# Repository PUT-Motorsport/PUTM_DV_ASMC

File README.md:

# ASMC: Autonomous System Main Controller

## Project Overview
The **ASMC (Autonomous System Main Controller)** is a central electronic control unit designed for a Formula Student racing vehicle. Its primary objective is to integrate the critical subsystems required for autonomous operation in compliance with the **Formula Student Rules 2026**. 

This board serves as a robust interface between the high-level autonomous compute unit and the vehicle's hardware, ensuring safety, reliable power distribution, and real-time status signaling.

## Key Functionalities

### 1. Power Management & Distribution
* **Peripheral Supply**: Provides regulated and protected power to sensors, actuators, and processing units necessary for the Autonomous System (AS).
* **LVS Compliance**: Operates within the Low Voltage System (LVS) limits (max 60V DC) and ensures proper grounding to the chassis.
* **Overcurrent Protection**: Integrated protection for all connected devices to prevent hardware failure during dynamic disciplines.

### 2. Autonomous System Signaling (ASSI & AMI)
* **ASSI Control**: Drives three Autonomous System Status Indicators (ASSI) positioned on the sides and rear of the vehicle.
* **Visual Logic**: Implements mandatory lighting patterns (e.g., 2–5 Hz flashing for "Driving" and "Emergency" states).
* **Acoustic Warning**: Manages the intermittent sound signal (80–90 dBA) required during the "AS Emergency" state.
* **Mission Selection**: Interfaces with the Autonomous Mission Indicator (AMI) to allow manual mission selection and status feedback without external tools.

### 3. Safety & Braking Interface (ASB/EBS)
* **EBS Data Processing**: Receives and processes critical data from the Emergency Brake System (EBS).
* **SCS Monitoring**: Continuously monitors System Critical Signals (SCS). Any failure (e.g., open circuit or data corruption) triggers a safe state transition within <500ms.
* **SDC & RES Integration**: Interfaces with the Shutdown Circuit (SDC) and the Remote Emergency System (RES) to allow for immediate vehicle shutdown.

## Technical Compliance
Designed according to the **T14 (Autonomous System)** and **T15 (Autonomous System Brake)** sections of the FS 2026 rulebook.

* **AS Status Flowchart**: The board logic follows the mandatory state machine (Off, Ready, Driving, Emergency, Finished).
* **Failsafe Design**: Ensures that loss of power or signal defaults the vehicle to an "AS Emergency" state, engaging the mechanical brakes.
* **Data Logging**: Provides necessary signal outputs to the official Formula Student Data Logger for competition transparency.

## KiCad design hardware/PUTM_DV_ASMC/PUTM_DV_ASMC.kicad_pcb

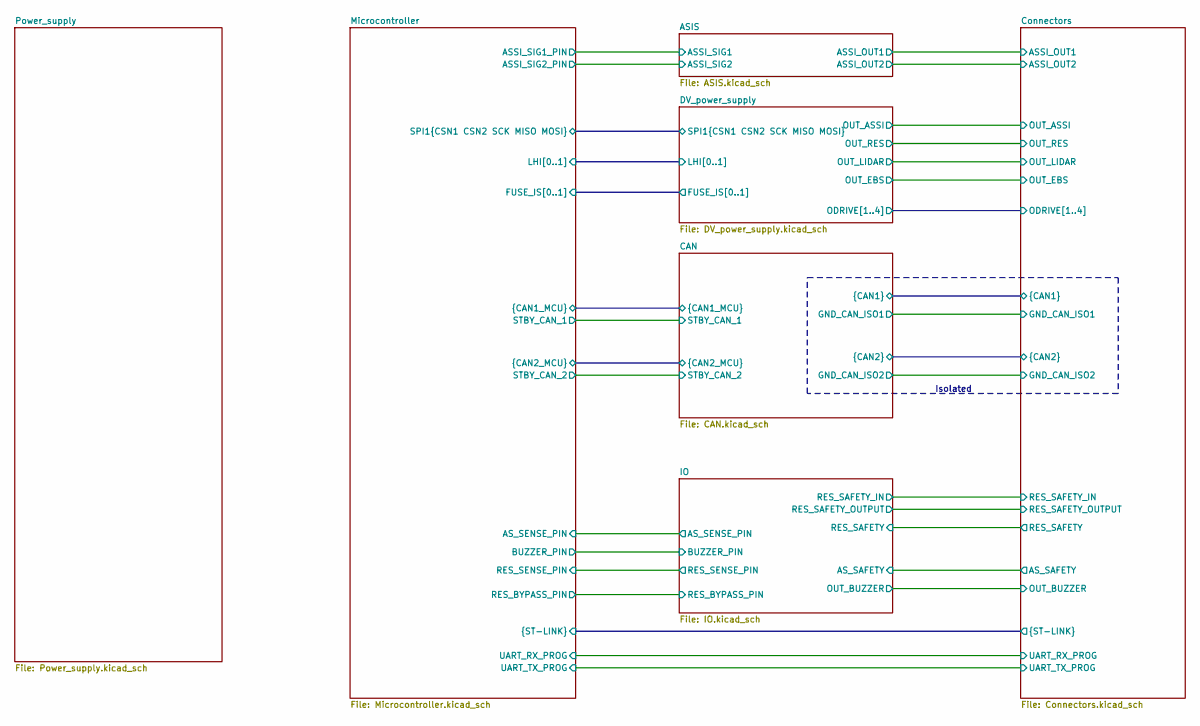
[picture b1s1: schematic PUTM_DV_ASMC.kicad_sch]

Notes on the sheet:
Isolated

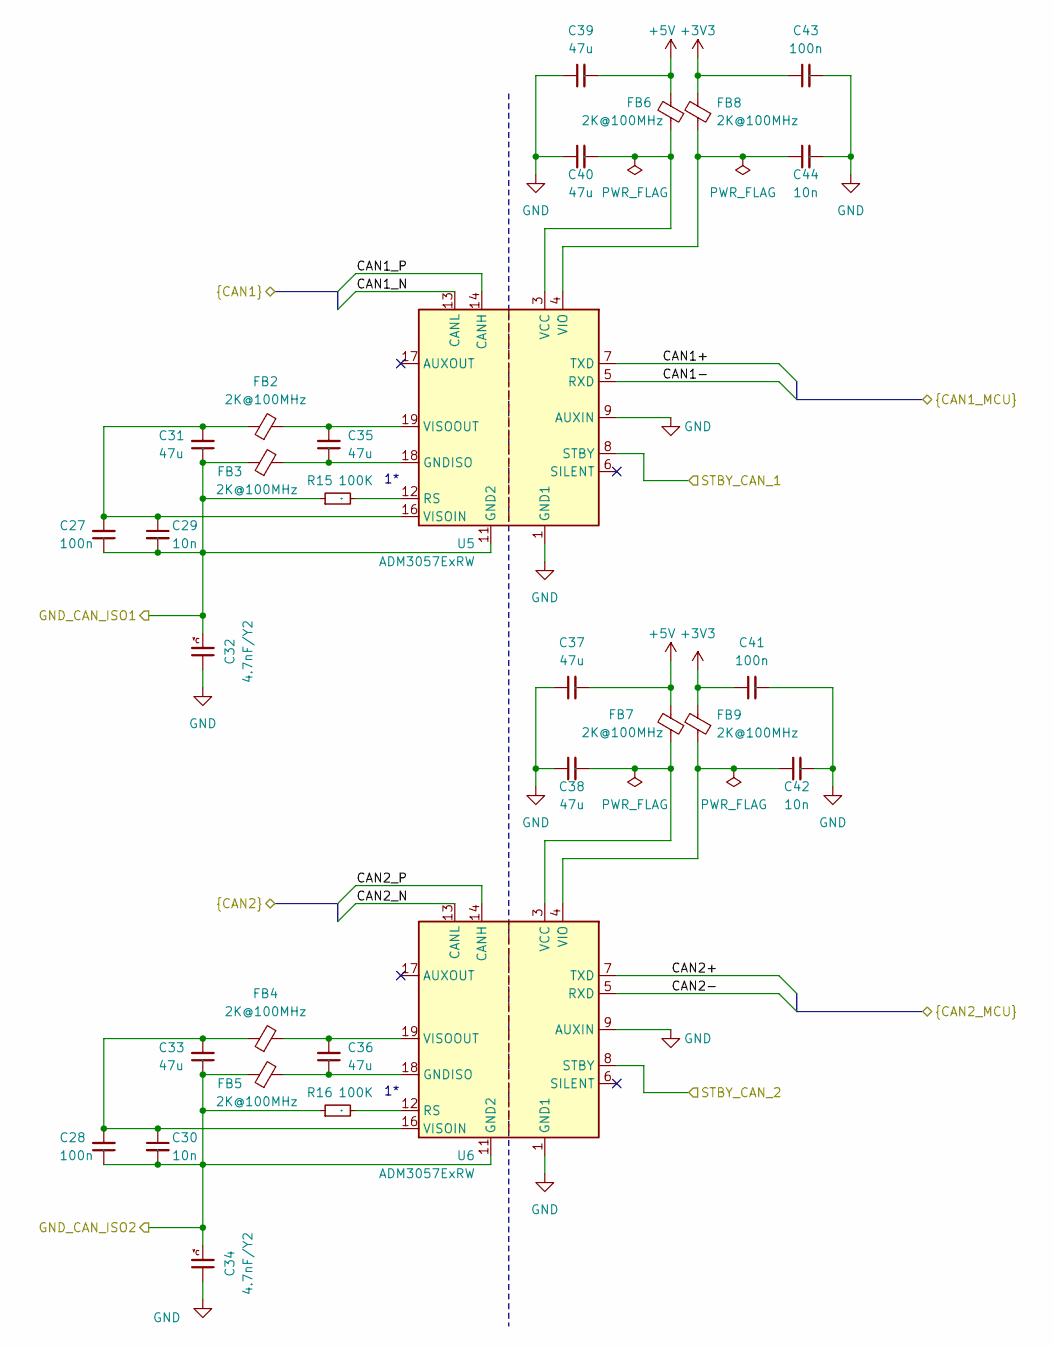
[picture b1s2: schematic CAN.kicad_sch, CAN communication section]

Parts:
C27, C28, C41, C43: 100n; C_0603_1608Metric_Pad1.08x0.95mm_HandSolder; Mouser Part Number .
C29, C30, C42, C44: 10n; C_0603_1608Metric_Pad1.08x0.95mm_HandSolder; Mouser Part Number .
C31, C33, C35, C36, C37, C38, C39, C40: 47u; C_0805_2012Metric_Pad1.18x1.45mm_HandSolder; Mouser Part Number .
C32, C34: 4.7nF/Y2; CAPC5728X280N; Mouser Part Number 791-S252B222K502CT
FB2, FB3, FB4, FB5, FB6, FB7, FB8, FB9: 2K@100MHz; L_0805_2012Metric_Pad1.05x1.20mm_HandSolder; Mouser Part Number 623-2508052027Y1
R15, R16: 100K; R_0603_1608Metric_Pad0.98x0.95mm_HandSolder; Mouser Part Number .
U5, U6: ADM3057ExRW; SOIC-20W_7.5x12.8mm_P1.27mm; Mouser Part Number 584-ADM3057EBRWZ

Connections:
+3V3: C41.1, C43.1, FB8.2, FB9.2; also elsewhere on the board
+5V: C37.2, C39.2, FB6.2, FB7.2; also elsewhere on the board
/CAN/CAN1+: U5.7 (TXD); also elsewhere on the board
/CAN/CAN1-: U5.5 (RXD); also elsewhere on the board
/CAN/CAN1_N: U5.13 (CANL); also elsewhere on the board
/CAN/CAN1_P: U5.14 (CANH); also elsewhere on the board
/CAN/CAN2+: U6.7 (TXD); also elsewhere on the board
/CAN/CAN2-: U6.5 (RXD); also elsewhere on the board
/CAN/CAN2_N: U6.13 (CANL); also elsewhere on the board
/CAN/CAN2_P: U6.14 (CANH); also elsewhere on the board
/CAN/GND_CAN_ISO1: C27.1, C29.2, C31.1, C32.2, FB3.1, R15.1, U5.11 (GND2), U5.15 (GND2); also elsewhere on the board
/CAN/GND_CAN_ISO2: C28.1, C30.2, C33.1, C34.2, FB5.1, R16.1, U6.11 (GND2), U6.15 (GND2); also elsewhere on the board
/CAN/STBY_CAN_1: U5.8 (STBY); also elsewhere on the board
/CAN/STBY_CAN_2: U6.8 (STBY); also elsewhere on the board
GND: C32.1, C34.1, C37.1, C38.1, C39.1, C40.1, C41.2, C42.2, C43.2, C44.2, U5.1 (GND1), U5.2 (GND1), U5.9 (AUXIN), U5.10 (GND1), U6.1 (GND1), U6.2 (GND1), U6.9 (AUXIN), U6.10 (GND1); also elsewhere on the board
unnamed: C35.1, FB3.2, U5.18 (GNDISO), U5.20 (GNDISO)
unnamed: C36.1, FB5.2, U6.18 (GNDISO), U6.20 (GNDISO)
unnamed: R15.2, U5.12 (RS)
unnamed: C40.2, FB6.1, U5.3 (VCC)
unnamed: C44.1, FB8.1, U5.4 (VIO)
unnamed: C27.2, C29.1, C31.2, FB2.1, U5.16 (VISOIN)
unnamed: C35.2, FB2.2, U5.19 (VISOOUT)
unnamed: R16.2, U6.12 (RS)
unnamed: C38.2, FB7.1, U6.3 (VCC)
unnamed: C42.1, FB9.1, U6.4 (VIO)
unnamed: C28.2, C30.1, C33.2, FB4.1, U6.16 (VISOIN)
unnamed: C36.2, FB4.2, U6.19 (VISOOUT)

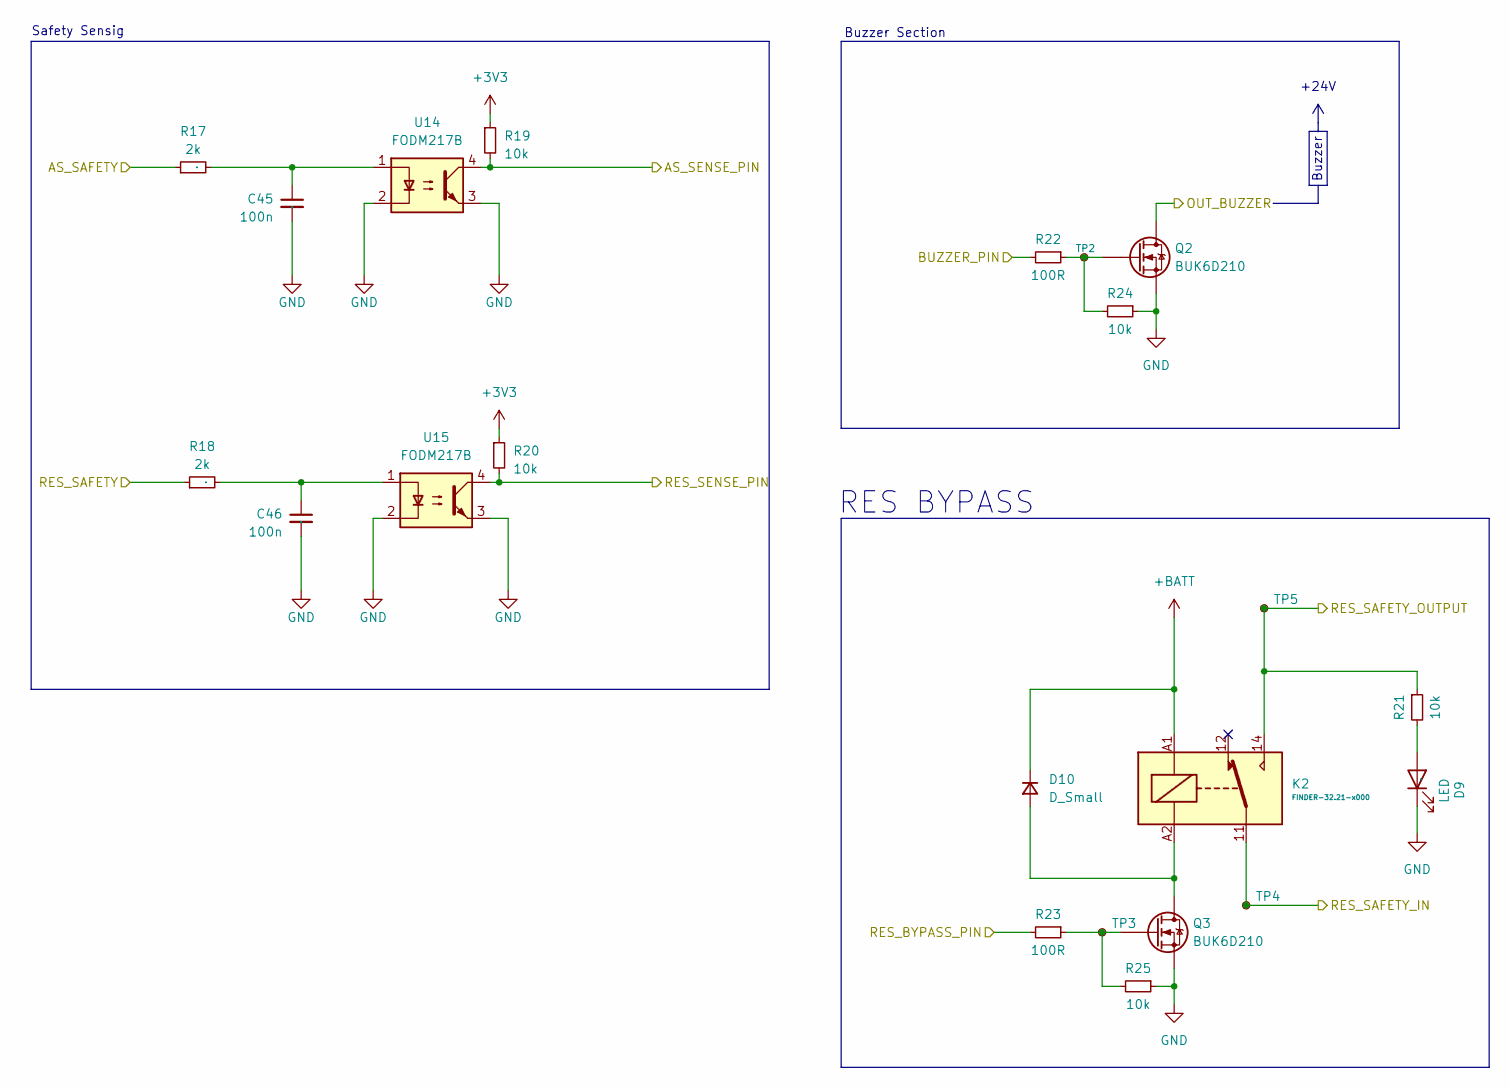
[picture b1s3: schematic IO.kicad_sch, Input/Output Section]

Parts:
C45, C46: 100n; C_0603_1608Metric_Pad1.08x0.95mm_HandSolder; Mouser Part Number .
D9: LED; LED_0603_1608Metric_Pad1.05x0.95mm_HandSolder; Mouser Part Number .
D10: D_Small; D_SOD-323_HandSoldering
K2: FINDER-32.21-x000; Relay_SPDT_Finder_32.21-x000
Q2, Q3: BUK6D210; Diodes_UDFN2020-6_Type-F
R17, R18: 2k; R_0603_1608Metric_Pad0.98x0.95mm_HandSolder; Mouser Part Number .
R19, R20: 10k; R_0603_1608Metric_Pad0.98x0.95mm_HandSolder; Mouser Part Number .
R21: 10k; R_1206_3216Metric_Pad1.30x1.75mm_HandSolder
R22, R23: 100R; R_0603_1608Metric
R24, R25: 10k; R_0603_1608Metric
TP2: TestPoint_Small; TestPoint_Pad_D1.0mm
TP3, TP4, TP5: TestPoint_Small
U14, U15: FODM217B; SOP-4_4.4x2.6mm_P1.27mm; Mouser Part Number 512-FODM217B

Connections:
+3V3: R19.1, R20.1; also elsewhere on the board
+BATT: D10.1 (K), K2.A1; also elsewhere on the board
/Connectors/AS_SAFETY: R17.1; also elsewhere on the board
/Connectors/OUT_BUZZER: Q2.1 (D), Q2.2 (D), Q2.5 (D), Q2.6 (D), Q2.7 (D); also elsewhere on the board
/Connectors/RES_SAFETY: R18.1; also elsewhere on the board
/Connectors/RES_SAFETY_IN: K2.11, TP4.1; also elsewhere on the board
/Connectors/RES_SAFETY_OUTPUT: K2.14, R21.1, TP5.1; also elsewhere on the board
/IO/AS_SENSE_PIN: R19.2, U14.4; also elsewhere on the board
/IO/BUZZER_PIN: R22.2; also elsewhere on the board
/IO/RES_BYPASS_PIN: R23.2; also elsewhere on the board
/IO/RES_SENSE_PIN: R20.2, U15.4; also elsewhere on the board
GND: C45.2, C46.2, D9.1 (K), Q2.4 (S), Q2.8 (S), Q3.4 (S), Q3.8 (S), R24.1, R25.1, U14.2, U14.3, U15.2, U15.3; also elsewhere on the board
unnamed: C45.1, R17.2, U14.1
unnamed: C46.1, R18.2, U15.1
unnamed: D9.2 (A), R21.2
unnamed: D10.2 (A), K2.A2, Q3.1 (D), Q3.2 (D), Q3.5 (D), Q3.6 (D), Q3.7 (D)
unnamed: Q2.3 (G), R22.1, R24.2, TP2.1 (1_1)
unnamed: Q3.3 (G), R23.1, R25.2, TP3.1

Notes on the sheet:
+24V
Buzzer Section
Buzzer
Safety Sensig
RES BYPASS

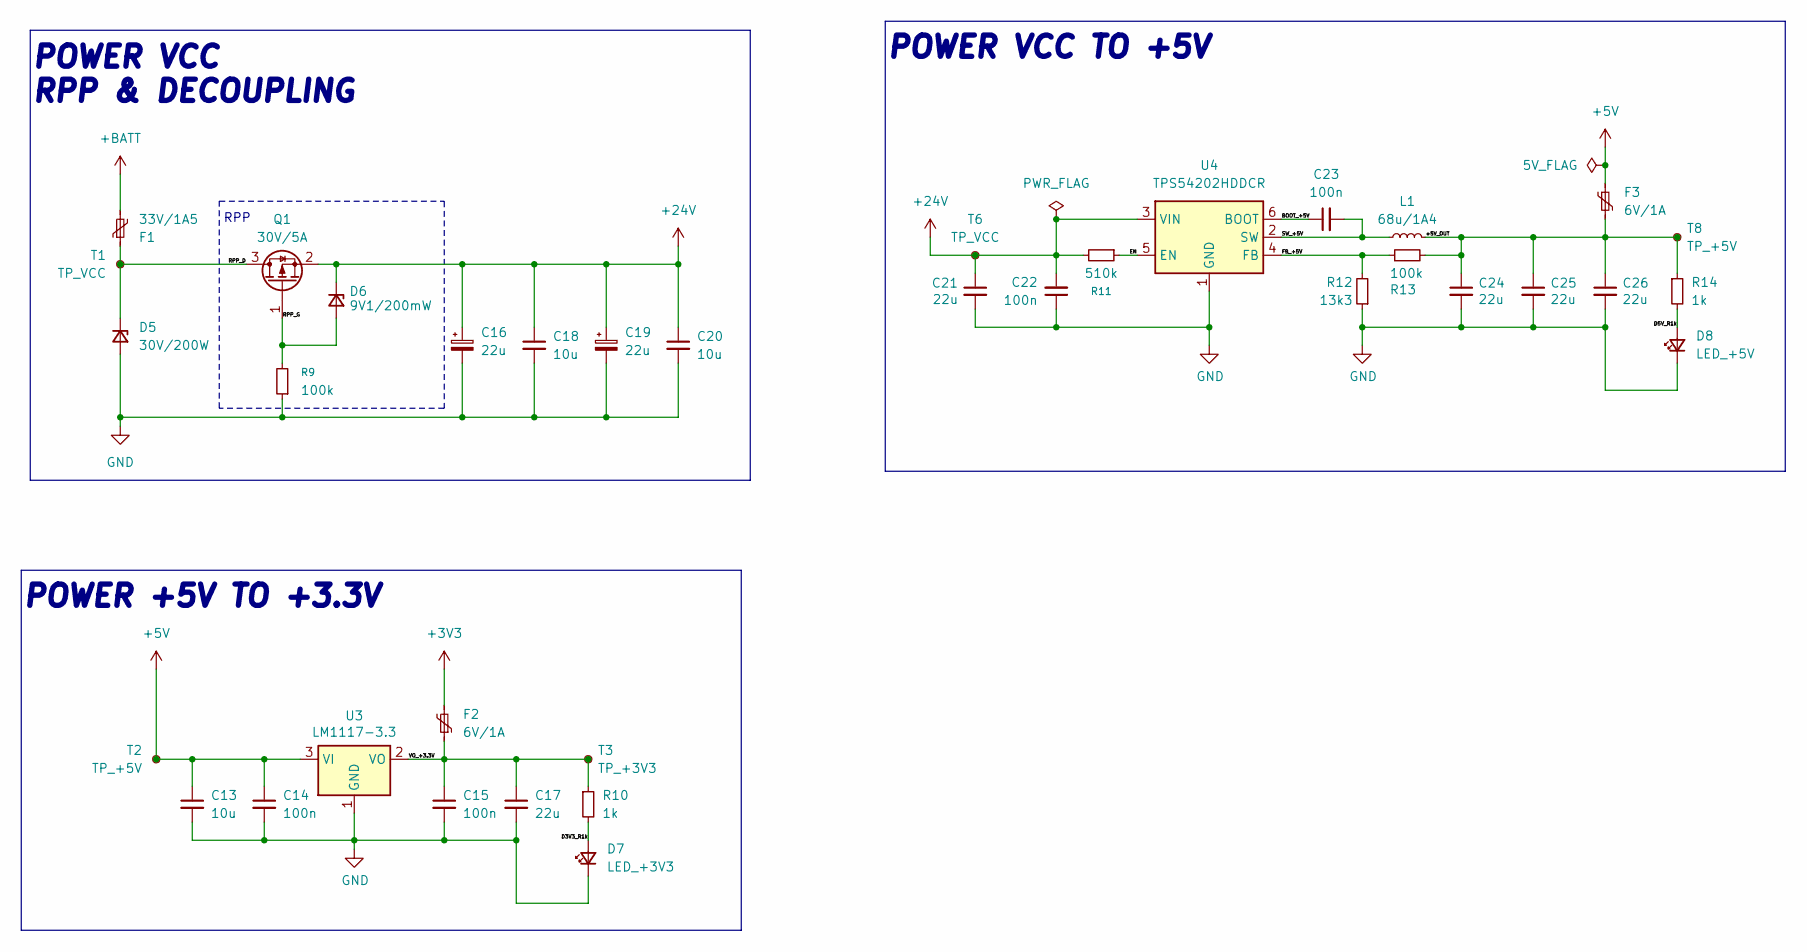
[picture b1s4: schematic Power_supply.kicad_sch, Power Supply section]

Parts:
C13, C18, C20: 10u; C_0805_2012Metric_Pad1.18x1.45mm_HandSolder; Mouser Part Number 81-GRM21BR61H106KE3L
C14, C15, C23: 100n; C_0603_1608Metric_Pad1.08x0.95mm_HandSolder; Mouser Part Number 81-GCJ188R71H104KA2D
C16, C19: 22u; CP_Elec_5x5.8; Mouser Part Number 647-UCM1H220MCL1GS
C17: 22u; C_0805_2012Metric_Pad1.18x1.45mm_HandSolder; Mouser Part Number 810-C2012X5R1V226MAC
C21, C24, C25, C26: 22u; C_0805_2012Metric_Pad1.18x1.45mm_HandSolder; Manufacturer_Part_Number CL21A107MQYNNWE; Mouser Part Number 810-C2012X5R1V226MAC
C22: 100n; C_0603_1608Metric_Pad1.08x0.95mm_HandSolder; Manufacturer_Part_Number C0603C104J3RACTU; Mouser Part Number 81-GCJ188R71H104KA2D
D5: 30V/200W; D_SOD-123; Mouser Part Number 750-TV02W260-G
D6: 9V1/200mW; D_SOD-323_HandSoldering; Mouser Part Number 833-MMXZ5239B-TP
D7: LED_+3V3; LED_0603_1608Metric_Pad1.05x0.95mm_HandSolder
D8: LED_+5V; LED_0603_1608Metric_Pad1.05x0.95mm_HandSolder
F1: 33V/1A5; Fuse_2920_7451Metric_Pad2.10x5.45mm_HandSolder; Mouser Part Number 530-0ZCF0075AF2C
F2, F3: 6V/1A; Fuse_0805_2012Metric_Pad1.15x1.40mm_HandSolder; Mouser Part Number 650-PICOSMDC050S-2
L1: 68u/1A4; L_TDK_VLS6045EX_VLS6045AF; Mouser Part Number 810-VLS6045EX-680M
Q1: 30V/5A; SOT-23-3; Mouser Part Number 78-SI2347DS-T1-GE3
R9: 100k; R_0603_1608Metric_Pad0.98x0.95mm_HandSolder; Mouser Part Number 71-CRCW0603100KFKEAH
R10, R14: 1k; R_0603_1608Metric_Pad0.98x0.95mm_HandSolder; Mouser Part Number 71-CRCW0603-1.0K-E3
R11: 510k; R_0603_1608Metric_Pad0.98x0.95mm_HandSolder; Mouser Part Number 71-CRCW0603J-510K-E3
R12: 13k3; R_0603_1608Metric_Pad0.98x0.95mm_HandSolder; Manufacturer_Part_Number RT0603DRE0713K3L; Mouser Part Number 71-CRCW0603-13.3K-E3
R13: 100k; R_0603_1608Metric_Pad0.98x0.95mm_HandSolder; Manufacturer_Part_Number RT0603DRE07100KL; Mouser Part Number 71-CRCW0603100KFKEAH
T1, T6: TP_VCC; TestPoint_Pad_1.0x1.0mm
T2, T8: TP_+5V; TestPoint_Pad_1.0x1.0mm
T3: TP_+3V3; TestPoint_Pad_1.0x1.0mm
U3: LM1117-3.3; SOT-223-3_TabPin2; Mouser Part Number 926-LM1117MPX3.3NOPB
U4: TPS54202HDDCR; SOT-23-6_Handsoldering; Mouser Part Number 595-TPS54202HDDCR

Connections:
+3V3: F2.2; also elsewhere on the board
+5V: C13.1, C14.1, F3.1, T2.1 (1_1), U3.3 (VI); also elsewhere on the board
+24V: C16.1, C18.1, C19.1, C20.1, C21.1, C22.2, D6.1 (K), Q1.2 (S), R11.2, T6.1 (1_1), U4.3 (VIN)
+BATT: F1.2; also elsewhere on the board
/Power_supply/+5V_OUT: C24.1, C25.1, C26.1, F3.2, L1.2, R13.2, R14.1, T8.1 (1_1)
/Power_supply/BOOT_+5V: C23.1, U4.6 (BOOT)
/Power_supply/D3V3_R1k: D7.2 (A), R10.2
/Power_supply/D5V_R1k: D8.2 (A), R14.2
/Power_supply/EN: R11.1, U4.5 (EN)
/Power_supply/FB_+5V: R12.2, R13.1, U4.4 (FB)
/Power_supply/RPP_D: D5.1 (K), F1.1, Q1.3 (D), T1.1 (1_1)
/Power_supply/RPP_G: D6.2 (A), Q1.1 (G), R9.2
/Power_supply/SW_+5V: C23.2, L1.1, U4.2 (SW)
/Power_supply/VO_+3.3V: C15.1, C17.1, F2.1, R10.1, T3.1 (1_1), U3.2 (VO)
GND: C13.2, C14.2, C15.2, C16.2, C17.2, C18.2, C19.2, C20.2, C21.2, C22.1, C24.2, C25.2, C26.2, D5.2 (A), D7.1 (K), D8.1 (K), R9.1, R12.1, U3.1 (GND), U4.1 (GND); also elsewhere on the board

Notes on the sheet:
POWER +5V TO +3.3V
POWER VCC RPP & DECOUPLING
POWER VCC TO +5V
RPP

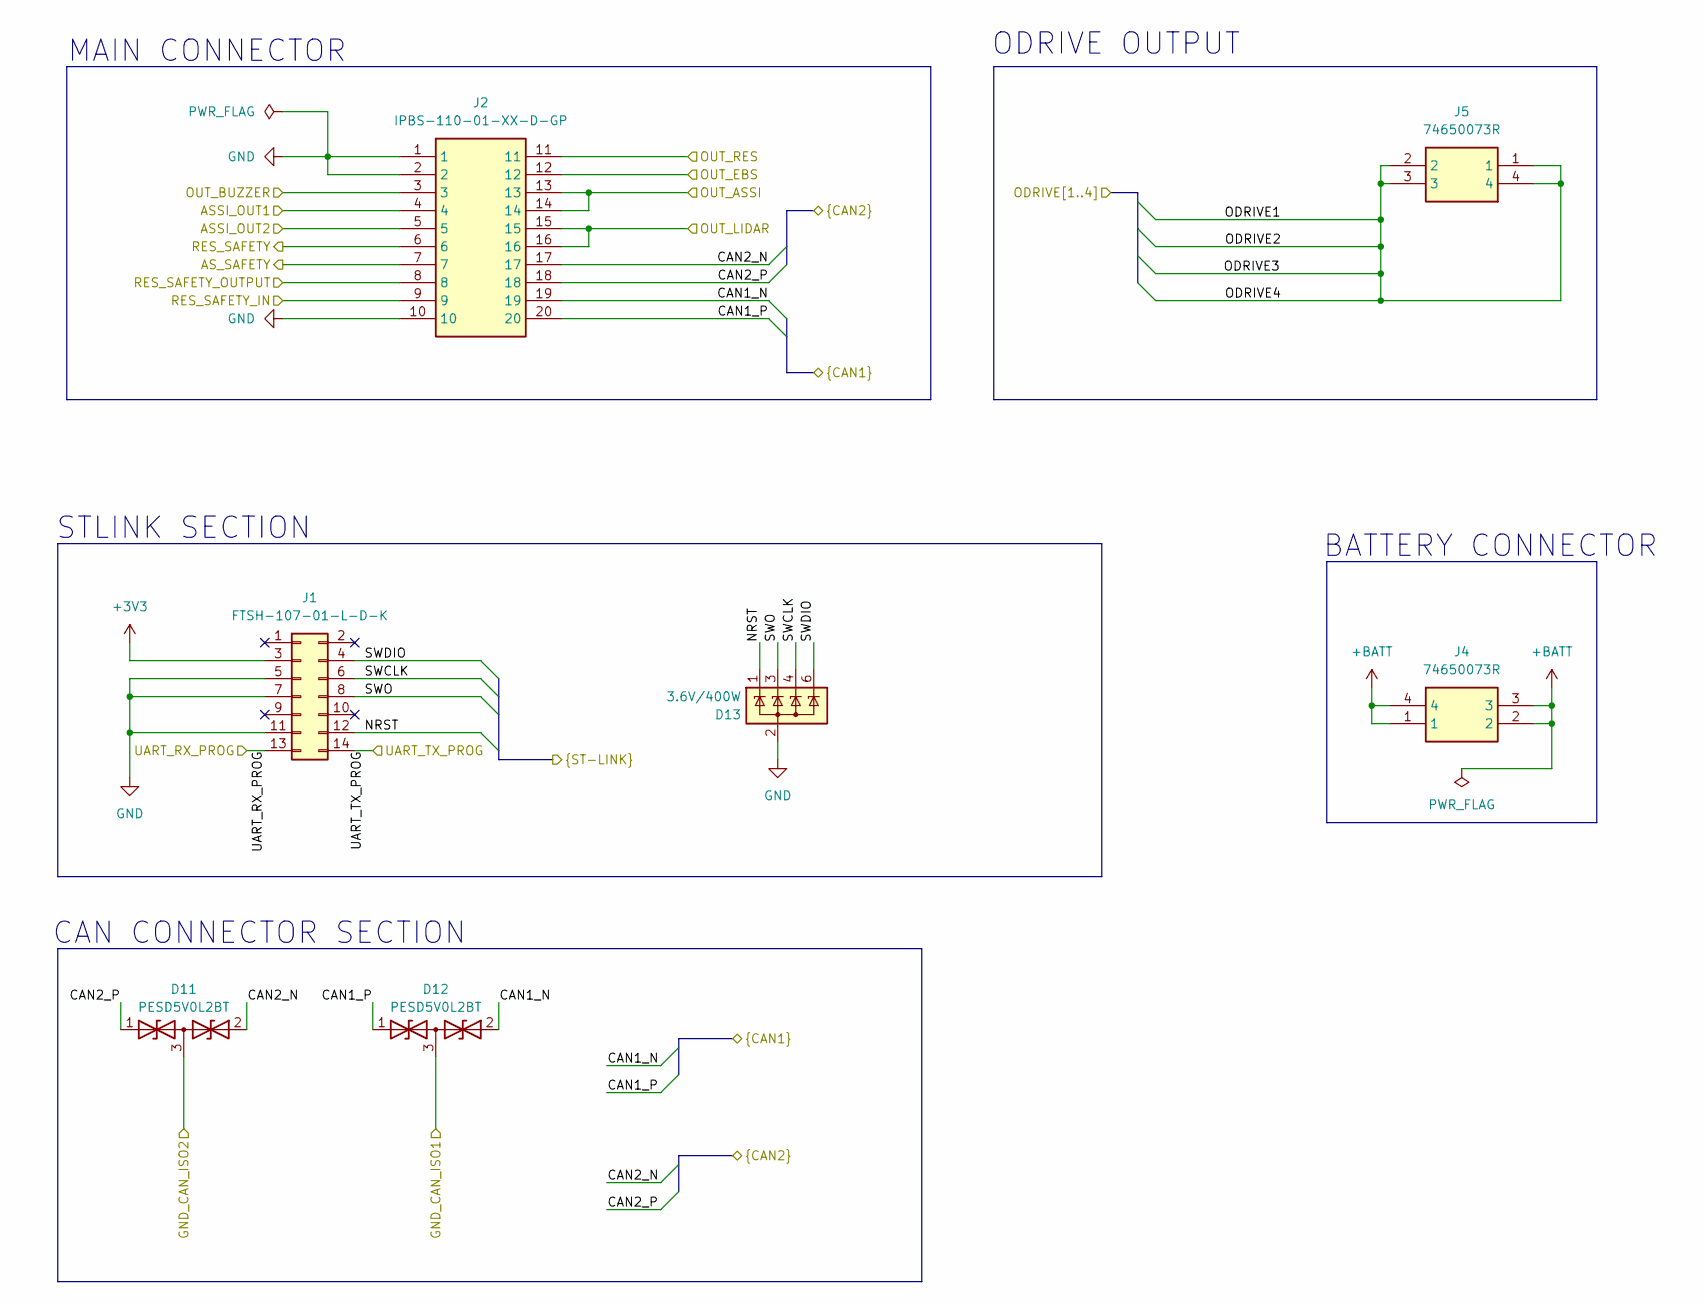
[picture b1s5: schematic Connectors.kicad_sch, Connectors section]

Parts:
D11, D12: PESD5V0L2BT; SOT-23_Handsoldering; Mouser Part Number 771-PESD5V0L2BT-QR
D13: 3.6V/400W; SOT-23-6; Manufacturer_Part_Number ESDS304DBVR; Mouser Part Number 595-ESDS304DBVR
J1: FTSH-107-01-L-D-K; FTSH-107-XX-YYY-D-K; Mouser Part Number 200-FTSH10701LDK
J2: IPBS-110-01-XX-D-GP; IPBS11001TDGP; PARTREV M; Mouser Part Number 200-IPBS11001TDGP
J4, J5: 74650073R; Mouser Part Number 710-74650073R

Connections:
+3V3: J1.3; also elsewhere on the board
+BATT: J4.1, J4.2, J4.3, J4.4; also elsewhere on the board
/ASIS/ASSI_OUT1: J2.4; also elsewhere on the board
/ASIS/ASSI_OUT2: J2.5; also elsewhere on the board
/CAN/CAN1_N: D12.2 (A2), J2.19; also elsewhere on the board
/CAN/CAN1_P: D12.1 (A1), J2.20; also elsewhere on the board
/CAN/CAN2_N: D11.2 (A2), J2.17; also elsewhere on the board
/CAN/CAN2_P: D11.1 (A1), J2.18; also elsewhere on the board
/CAN/GND_CAN_ISO1: D12.3 (common); also elsewhere on the board
/CAN/GND_CAN_ISO2: D11.3 (common); also elsewhere on the board
/Connectors/AS_SAFETY: J2.7; also elsewhere on the board
/Connectors/NRST: D13.1 (A), J1.12; also elsewhere on the board
/Connectors/ODRIVE4: J5.1, J5.2, J5.3, J5.4; also elsewhere on the board
/Connectors/OUT_ASSI: J2.13, J2.14; also elsewhere on the board
/Connectors/OUT_BUZZER: J2.3; also elsewhere on the board
/Connectors/OUT_EBS: J2.12; also elsewhere on the board
/Connectors/OUT_LIDAR: J2.15, J2.16; also elsewhere on the board
/Connectors/OUT_RES: J2.11; also elsewhere on the board
/Connectors/RES_SAFETY: J2.6; also elsewhere on the board
/Connectors/RES_SAFETY_IN: J2.9; also elsewhere on the board
/Connectors/RES_SAFETY_OUTPUT: J2.8; also elsewhere on the board
/Connectors/SWCLK: D13.4 (A), J1.6; also elsewhere on the board
/Connectors/SWDIO: D13.6 (A), J1.4; also elsewhere on the board
/Connectors/SWO: D13.3 (A), J1.8; also elsewhere on the board
/Connectors/UART_RX_PROG: J1.13; also elsewhere on the board
/Connectors/UART_TX_PROG: J1.14; also elsewhere on the board
GND: D13.2 (K), D13.5 (NC), J1.5, J1.7, J1.11, J2.1, J2.2, J2.10; also elsewhere on the board

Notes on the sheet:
BATTERY CONNECTOR
STLINK SECTION
CAN CONNECTOR SECTION
MAIN CONNECTOR
ODRIVE OUTPUT

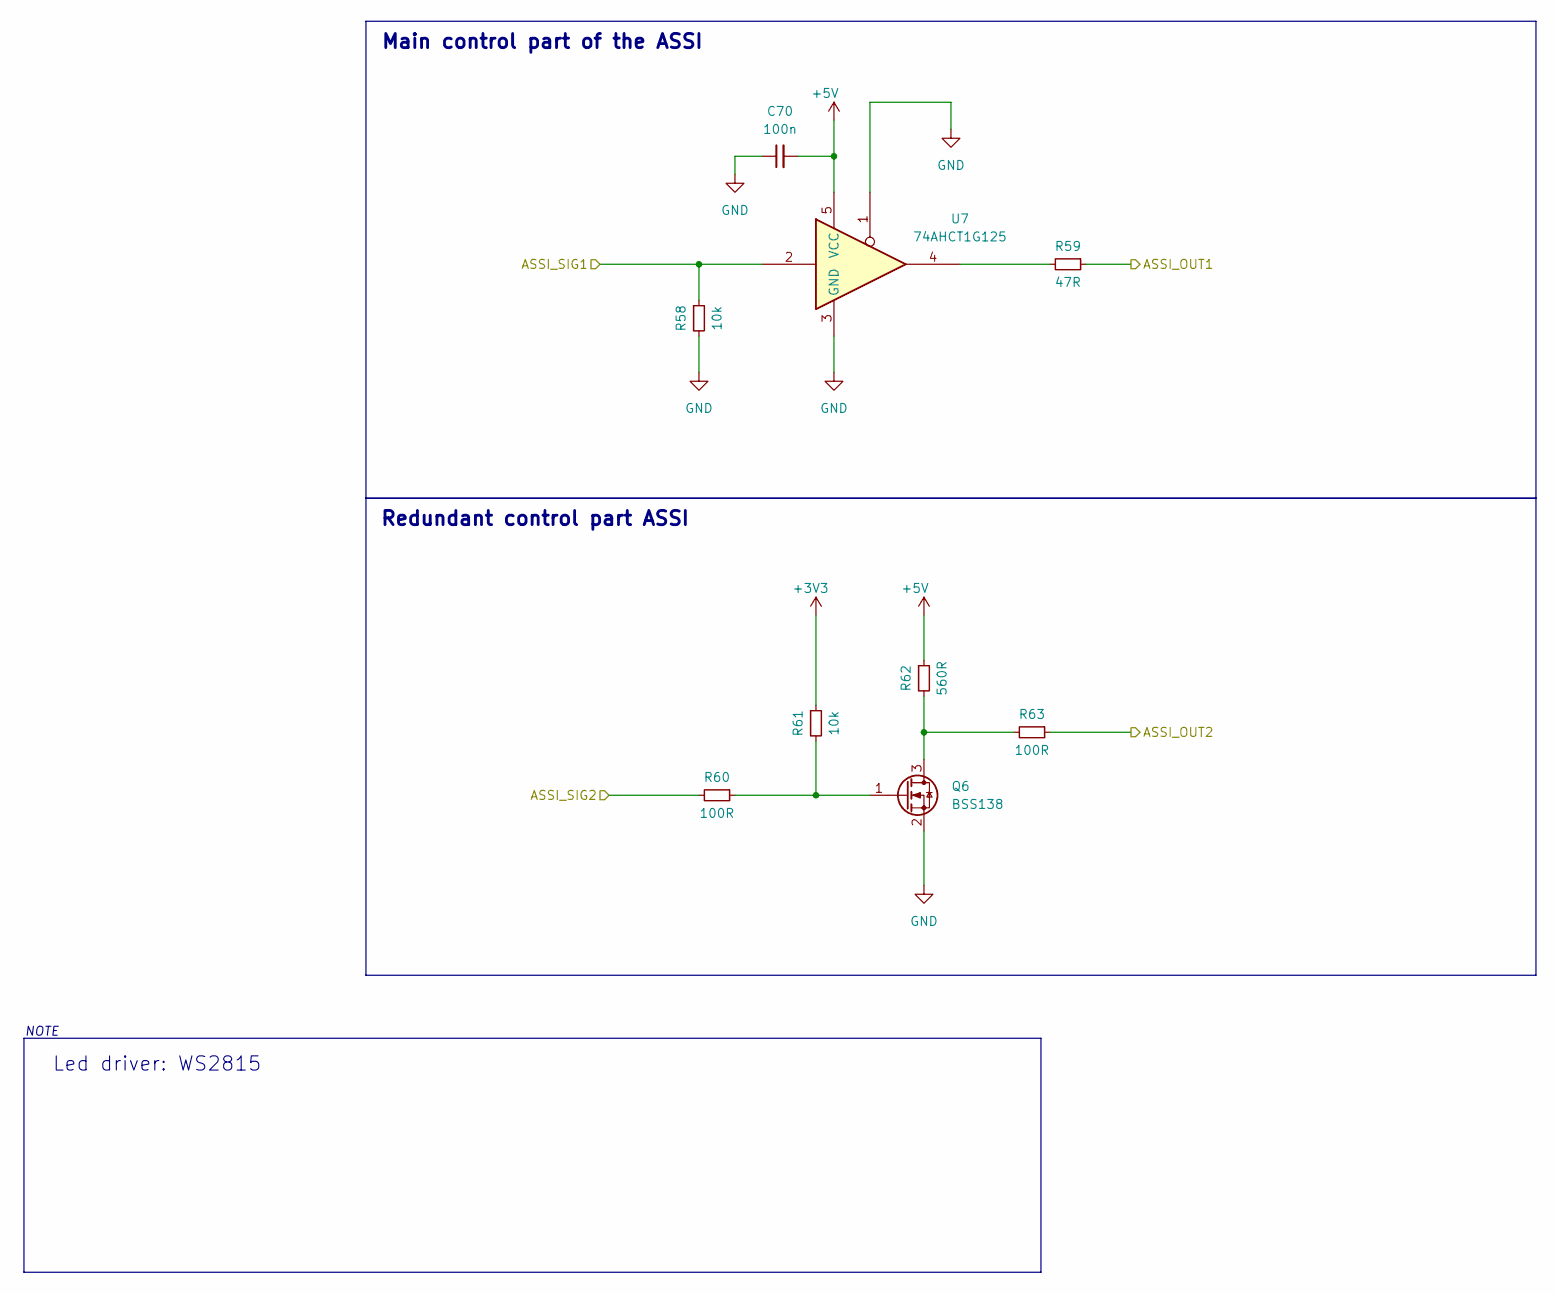
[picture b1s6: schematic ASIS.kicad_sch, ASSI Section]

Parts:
C70: 100n; C_0603_1608Metric_Pad1.08x0.95mm_HandSolder; Mouser Part Number .
Q6: BSS138; SOT-23
R58, R61: 10k; R_0603_1608Metric
R59: 47R; R_0603_1608Metric
R60, R63: 100R; R_0603_1608Metric
R62: 560R; R_0603_1608Metric
U7: 74AHCT1G125; SOT-23-5

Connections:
+3V3: R61.1; also elsewhere on the board
+5V: C70.2, R62.1, U7.5 (VCC); also elsewhere on the board
/ASIS/ASSI_OUT1: R59.1; also elsewhere on the board
/ASIS/ASSI_OUT2: R63.1; also elsewhere on the board
/ASIS/ASSI_SIG1: R58.1, U7.2; also elsewhere on the board
/ASIS/ASSI_SIG2: R60.2; also elsewhere on the board
GND: C70.1, Q6.2 (S), R58.2, U7.1, U7.3 (GND); also elsewhere on the board
unnamed: Q6.3 (D), R62.2, R63.2
unnamed: Q6.1 (G), R60.1, R61.2
unnamed: R59.2, U7.4

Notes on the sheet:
Led driver: WS2815
Redundant control part ASSI
Main control part of the ASSI
NOTE

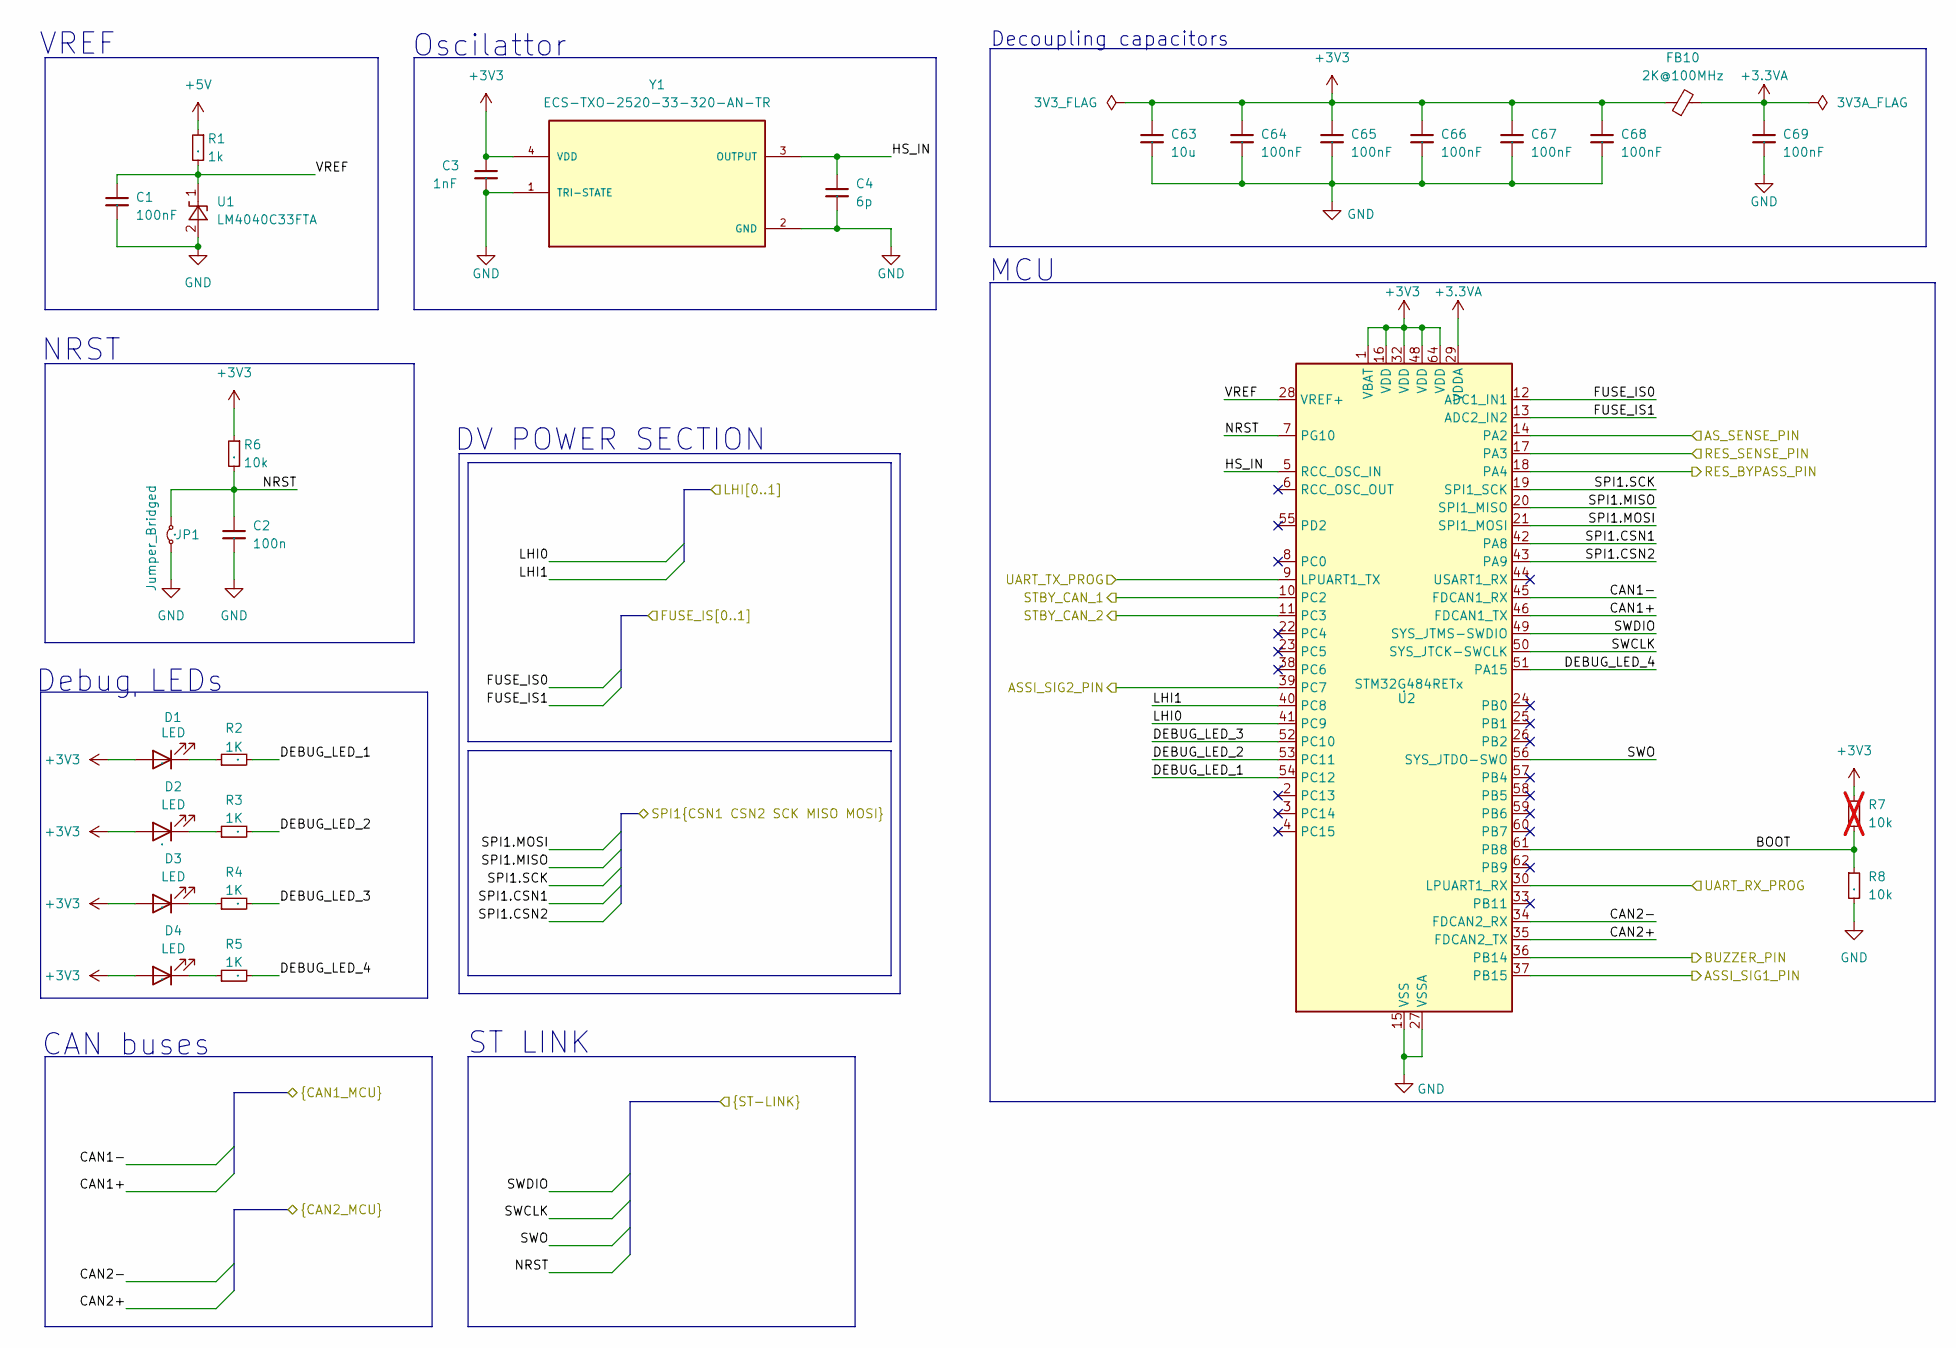
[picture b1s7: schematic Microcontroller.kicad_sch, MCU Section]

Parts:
C1, C64, C65, C66, C67, C68, C69: 100nF; C_0603_1608Metric_Pad1.08x0.95mm_HandSolder; Mouser Part Number .
C2: 100n; C_0603_1608Metric; Mouser Part Number .
C3: 1nF; C_0603_1608Metric_Pad1.08x0.95mm_HandSolder; Mouser Part Number .
C4: 6p; C_0603_1608Metric_Pad1.08x0.95mm_HandSolder; Mouser Part Number .
C63: 10u; C_0805_2012Metric_Pad1.18x1.45mm_HandSolder; Mouser Part Number .
D1, D2, D3, D4: LED; LED_0603_1608Metric_Pad1.05x0.95mm_HandSolder; Mouser Part Number .
FB10: 2K@100MHz; L_0805_2012Metric_Pad1.05x1.20mm_HandSolder; Mouser Part Number 623-2508052027Y1
JP1: Jumper_Bridged; SolderJumper-2_P1.3mm_Open_TrianglePad1.0x1.5mm; Mouser Part Number .
R1: 1k; R_0603_1608Metric; Mouser Part Number .
R2, R3, R4, R5: 1K; R_0603_1608Metric_Pad0.98x0.95mm_HandSolder; Mouser Part Number .
R6, R8: 10k; R_0603_1608Metric; Mouser Part Number .
R7: 10k; R_0603_1608Metric; Mouser Part Number .; not fitted
U1: LM4040C33FTA; SOT-23; Mouser Part Number 621-LM4040C33FTA
U2: STM32G484RETx; LQFP-64_10x10mm_P0.5mm; Mouser Part Number .
Y1: ECS-TXO-2520-33-320-AN-TR; OSC_ECS-TXO-2520-33-320-AN-TR; PARTREV 2017

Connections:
+3.3VA: C69.1, FB10.2, U2.29 (VDDA)
+3V3: C3.1, C63.1, C64.1, C65.1, C66.1, C67.1, C68.1, D1.2 (A), D2.2 (A), D3.2 (A), D4.2 (A), FB10.1, R6.1, R7.1, U2.1 (VBAT), U2.16 (VDD), U2.32 (VDD), U2.48 (VDD), U2.64 (VDD), Y1.4 (VDD); also elsewhere on the board
+5V: R1.1; also elsewhere on the board
/ASIS/ASSI_SIG1: U2.37 (PB15); also elsewhere on the board
/ASIS/ASSI_SIG2: U2.39 (PC7); also elsewhere on the board
/CAN/CAN1+: U2.46 (FDCAN1_TX); also elsewhere on the board
/CAN/CAN1-: U2.45 (FDCAN1_RX); also elsewhere on the board
/CAN/CAN2+: U2.35 (FDCAN2_TX); also elsewhere on the board
/CAN/CAN2-: U2.34 (FDCAN2_RX); also elsewhere on the board
/CAN/STBY_CAN_1: U2.10 (PC2); also elsewhere on the board
/CAN/STBY_CAN_2: U2.11 (PC3); also elsewhere on the board
/Connectors/NRST: C2.1, JP1.2 (B), R6.2, U2.7 (PG10); also elsewhere on the board
/Connectors/SWCLK: U2.50 (SYS_JTCK-SWCLK); also elsewhere on the board
/Connectors/SWDIO: U2.49 (SYS_JTMS-SWDIO); also elsewhere on the board
/Connectors/SWO: U2.56 (SYS_JTDO-SWO); also elsewhere on the board
/Connectors/UART_RX_PROG: U2.30 (LPUART1_RX); also elsewhere on the board
/Connectors/UART_TX_PROG: U2.9 (LPUART1_TX); also elsewhere on the board
/DV_power_supply/FUSE_IS0: U2.12 (ADC1_IN1); also elsewhere on the board
/DV_power_supply/FUSE_IS1: U2.13 (ADC2_IN2); also elsewhere on the board
/DV_power_supply/LHI0: U2.41 (PC9); also elsewhere on the board
/DV_power_supply/LHI1: U2.40 (PC8); also elsewhere on the board
/DV_power_supply/SPI1.CSN1: U2.42 (PA8); also elsewhere on the board
/DV_power_supply/SPI1.CSN2: U2.43 (PA9); also elsewhere on the board
/DV_power_supply/SPI1.MISO: U2.20 (SPI1_MISO); also elsewhere on the board
/DV_power_supply/SPI1.MOSI: U2.21 (SPI1_MOSI); also elsewhere on the board
/DV_power_supply/SPI1.SCK: U2.19 (SPI1_SCK); also elsewhere on the board
/IO/AS_SENSE_PIN: U2.14 (PA2); also elsewhere on the board
/IO/BUZZER_PIN: U2.36 (PB14); also elsewhere on the board
/IO/RES_BYPASS_PIN: U2.18 (PA4); also elsewhere on the board
/IO/RES_SENSE_PIN: U2.17 (PA3); also elsewhere on the board
/Microcontroller/BOOT: R7.2, R8.1, U2.61 (PB8)
/Microcontroller/DEBUG_LED_1: R2.2, U2.54 (PC12)
/Microcontroller/DEBUG_LED_2: R3.2, U2.53 (PC11)
/Microcontroller/DEBUG_LED_3: R4.2, U2.52 (PC10)
/Microcontroller/DEBUG_LED_4: R5.2, U2.51 (PA15)
/Microcontroller/HS_IN: C4.1, U2.5 (RCC_OSC_IN), Y1.3 (OUTPUT)
/Microcontroller/VREF: C1.1, R1.2, U1.1 (K), U2.28 (VREF+)
GND: C1.2, C2.2, C3.2, C4.2, C63.2, C64.2, C65.2, C66.2, C67.2, C68.2, C69.2, JP1.1 (A), R8.2, U1.2 (A), U2.15 (VSS), U2.27 (VSSA), U2.31 (VSS), U2.47 (VSS), U2.63 (VSS), Y1.1 (TRI-STATE), Y1.2 (GND); also elsewhere on the board
unnamed: D1.1 (K), R2.1
unnamed: D2.1 (K), R3.1
unnamed: D3.1 (K), R4.1
unnamed: D4.1 (K), R5.1

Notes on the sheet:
DV POWER SECTION
NRST
Decoupling capacitors
Debug LEDs
CAN buses
Oscilattor
MCU
VREF
ST LINK
